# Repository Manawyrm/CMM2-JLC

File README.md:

Colour Maximite 2 - JLC-ready design
=============================

#### Overview

This is a open-source hardware clone PCB of the [Colour Maximite 2](https://geoffg.net/maximite.html) computer.  
It's fully compatible to the original firmware and software.  

- Designed for automated assembly at [JLCPCB](https://jlcpcb.com/DDE), everything except the connectors can be machine assembled.  
- USB-C port (instead of USB-B) for serial and power  
- microSD socket instead of full-size SD socket  
- STM32 and SDRAM directly onboard, no expensive evaluation board needed  

#### Bill of materials

[Interactive BOM](https://tbspace.de/content/downloads/ibom_cmm2_reve.html)

| Description | Part No.  | Links  |
| :-------:|-------------| -----:|
| 3.5mm audio jack | XKB PJ-3270 | [LCSC](https://lcsc.com/product-detail/Audio-Video-Connectors_XKB-Connectivity-PJ-3270_C381134.html) |
| microSD socket | HOAUC HYC77-TF09-200 | [LCSC](https://lcsc.com/product-detail/Card-Sockets-Connectors_HOAUC-HYC77-TF09-200_C341092.html)  |
| USB-C connector | Jing C167321 | [LCSC](https://lcsc.com/product-detail/USB-Connectors_Jing-Extension-of-the-Electronic-Co-C167321_C167321.html)  |
| USB-A connector | Jing C42650 | [LCSC](https://lcsc.com/product-detail/USB-Connectors_Jing-Extension-of-the-Electronic-Co-C42650_C42650.html)  |
| 40pin IDC | BOOMELE C9138 | [LCSC](https://lcsc.com/product-detail/IDC-Connectors_BOOMELE-Boom-Precision-Elec-C9138_C9138.html)  |
| VGA connector | CONNFLY DS1038-15FBNSiA74-0CC | [LCSC](https://lcsc.com/product-detail/D-Sub-Connectors_CONNFLY-Elec-DS1038-15FBNSiA74-0CC_C75754.html)  |

#### Footprint credits
| Author | Components  |
| ----- |-------|
| [Tobias Schramm](https://github.com/TobleMiner) | CR2032 Holder, 3.5mm Audiojack, MicroSD socket, reset button |
| [Jan Henrik Hemsing](https://github.com/Jan--Henrik) | Nunchuck connector |

#### Rev.A Errata
- Missing mounting holes
- SDRAM pinout is missing A12 line 
(causes instability, fixed in Rev.B, workaround with enamelled copper wire of the same length as the other traces)
- SRV05 diode package had the Pin 1 indicator at Pin 6.  
- Nunchuck footprint is reversed

#### Rev. B Errata
- KiCad Bug caused data corruption in PCB files, board files were reset back to pre-RevA state (missing via stitching). Will still work. 
- SRV05 diode package had the Pin 1 indicator at Pin 6.  
- Nunchuck footprint is reversed

#### Rev. C Errata
- SRV05 diode package had the Pin 1 indicator at Pin 6.  
- Nunchuck footprint is reversed

#### Rev. D Errata
- SRV05 diode package had the Pin 1 indicator at Pin 6.

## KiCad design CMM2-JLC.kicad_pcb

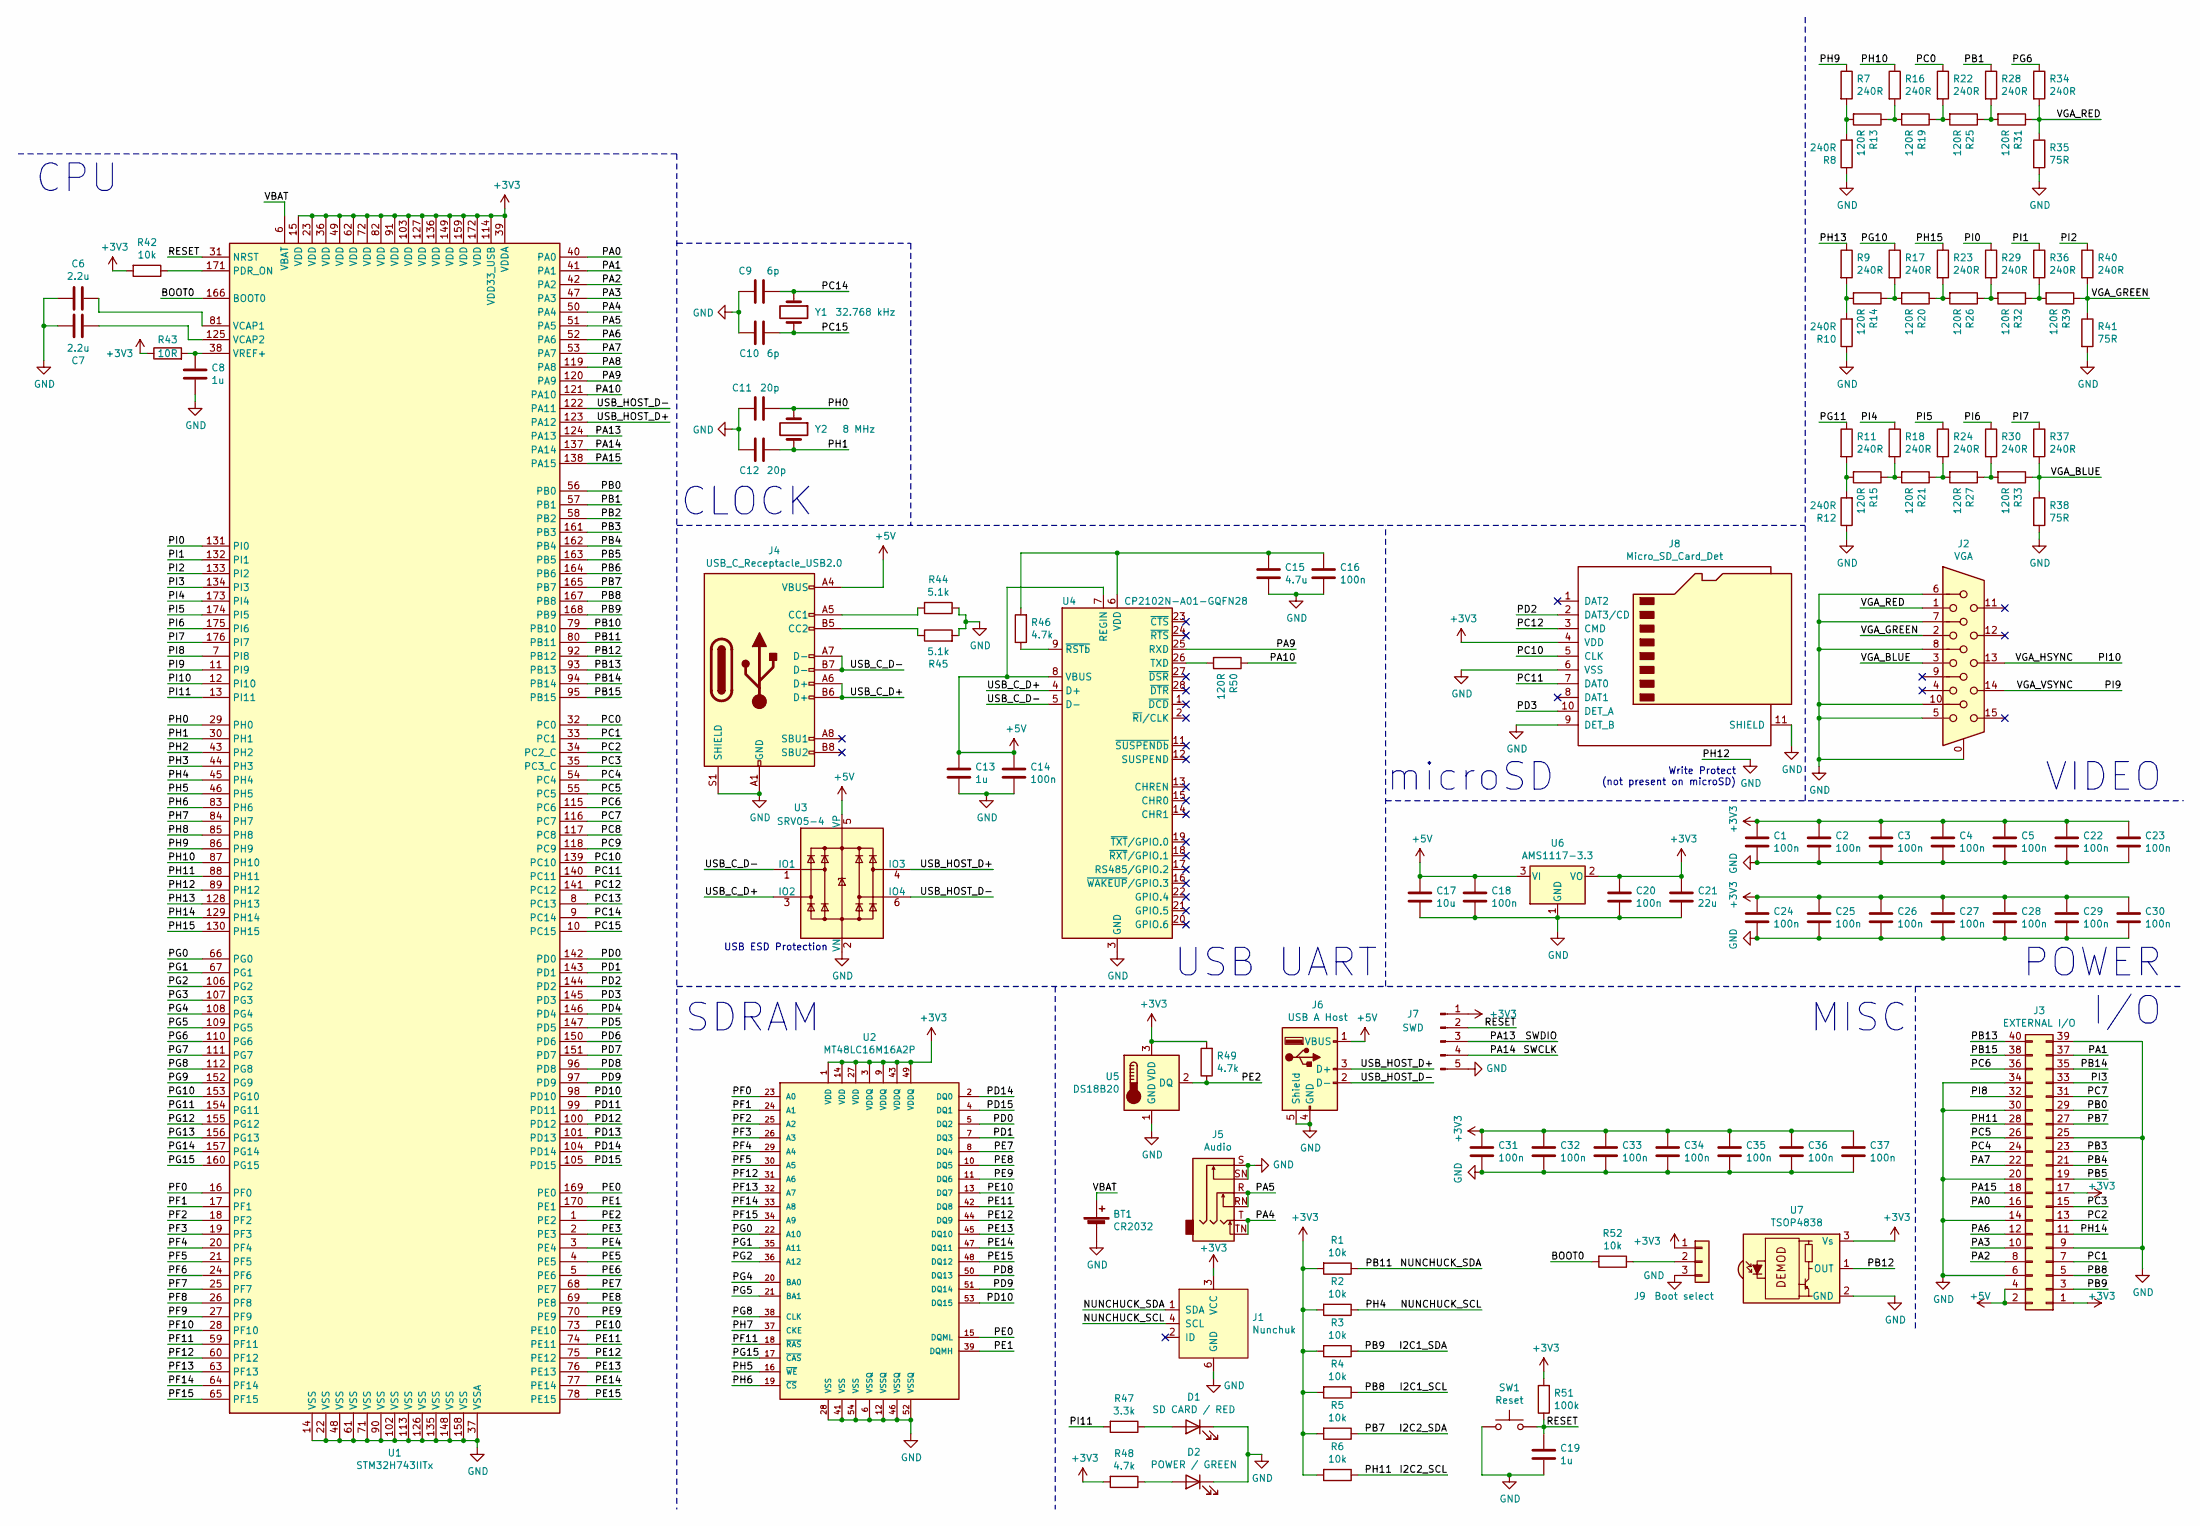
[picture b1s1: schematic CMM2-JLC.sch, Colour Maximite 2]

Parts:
BT1: CR2032; BatteryHolder_CR2032-BS-6-1; LCSC C70377
C1, C2, C3, C4, C5, C14, C16, C18, C20, C22, C23, C24, C25, C26, C27, C28, C29, C30, C31, C32, C33, C34, C35, C36, C37: 100n; C_0402_1005Metric; LCSC C1525
C6, C7: 2.2u; C_0603_1608Metric; LCSC C23630
C8, C13, C19: 1u; C_0402_1005Metric; LCSC C52923
C9, C10: 6p; C_0402_1005Metric; LCSC C30274
C11, C12: 20p; C_0402_1005Metric; LCSC C1554
C15: 4.7u; C_0402_1005Metric; LCSC C23733
C17: 10u; C_0603_1608Metric; LCSC C19702
C21: 22u; C_0603_1608Metric; LCSC C59461
D1: SD CARD / RED; LED_0603_1608Metric; LCSC C2286
D2: POWER / GREEN; LED_0603_1608Metric; LCSC C72043
J1: Nunchuk; nunchuck
J2: VGA; DSUB-15-HD_Female_Horizontal_P2.29x2,54mm_EdgePinOffset8.63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
J3: EXTERNAL I/O; IDC-Header_2x20_P2.54mm_Vertical
J4: USB_C_Receptacle_USB2.0; USB_C_Receptacle_Palconn_UTC16-G
J5: Audio; PJ-3270
J6: USB A Host; USB_A_Molex_67643_Horizontal
J7: SWD; PinHeader_1x05_P2.54mm_Vertical
J8: Micro_SD_Card_Det; HOAUC_HYC77-TF09-200
J9: Boot select; PinHeader_1x03_P2.54mm_Vertical
R1, R2, R3, R4, R5, R6, R42, R52: 10k; R_0402_1005Metric; LCSC C25744
R7, R8, R9, R10, R11, R12, R16, R17, R18, R22, R23, R24, R28, R29, R30, R34, R36, R37, R40: 240R; R_0603_1608Metric; LCSC C23350
R13, R14, R15, R19, R20, R21, R25, R26, R27, R31, R32, R33, R39, R50: 120R; R_0603_1608Metric; LCSC C22787
R35, R38, R41: 75R; R_0603_1608Metric; LCSC C4275
R43: 10R; R_0402_1005Metric; LCSC C25077
R44, R45: 5.1k; R_0402_1005Metric; LCSC C25905
R46, R48, R49: 4.7k; R_0402_1005Metric; LCSC C25900
R47: 3.3k; R_0402_1005Metric; LCSC C25890
R51: 100k; R_0402_1005Metric; LCSC C25741
SW1: Reset; TS-1187A-X-X-X; LCSC C318887
U1: STM32H743IITx; LQFP-176_24x24mm_P0.5mm; LCSC C89597
U2: MT48LC16M16A2P; TSOP-II-54_22.2x10.16mm_P0.8mm; LCSC C26393
U3: SRV05-4; SOT-23-6; LCSC C85364
U4: CP2102N-A01-GQFN28; QFN-28-1EP_5x5mm_P0.5mm_EP3.35x3.35mm; LCSC C6568
U5: DS18B20; TO-92_Inline
U6: AMS1117-3.3; SOT-223-3_TabPin2; LCSC C6186
U7: TSOP4838; Vishay_MOLD-3Pin
Y1: 32.768 kHz; Crystal_SMD_3215-2Pin_3.2x1.5mm; LCSC C32346
Y2: 8 MHz; Crystal_SMD_5032-2Pin_5.0x3.2mm; LCSC C115962

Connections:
+3V3: C1.1, C2.1, C3.1, C4.1, C5.1, C20.1, C21.1, C22.1, C23.1, C24.1, C25.1, C26.1, C27.1, C28.1, C29.1, C30.1, C31.1, C32.1, C33.1, C34.1, C35.1, C36.1, C37.1, J1.3 (VCC), J3.1, J3.17, J7.1, J8.4 (VDD), J9.1, R1.2, R2.2, R3.2, R4.2, R5.2, R6.2, R42.2, R43.1, R48.2, R49.2, R51.2, U1.15 (VDD), U1.23 (VDD), U1.36 (VDD), U1.39 (VDDA), U1.49 (VDD), U1.62 (VDD), U1.72 (VDD), U1.82 (VDD), U1.91 (VDD), U1.103 (VDD), U1.114 (VDD33_USB), U1.127 (VDD), U1.136 (VDD), U1.149 (VDD), U1.159 (VDD), U1.172 (VDD), U2.1 (VDD), U2.3 (VDDQ), U2.9 (VDDQ), U2.14 (VDD), U2.27 (VDD), U2.43 (VDDQ), U2.49 (VDDQ), U5.3 (VDD), U6.2 (VO), U7.3 (Vs)
+5V: C13.1, C14.1, C17.1, C18.1, J3.2, J3.4, J4.A4 (VBUS), J4.A9 (VBUS), J4.B4 (VBUS), J4.B9 (VBUS), J6.1 (VBUS), U3.5 (VP), U4.7 (REGIN), U4.8 (VBUS), U6.3 (VI)
/BOOT0: R52.2, U1.166 (BOOT0)
/I2C1_SCL: J3.5, R4.1, U1.167 (PB8)
/I2C1_SDA: J3.3, R3.1, U1.168 (PB9)
/I2C2_SCL: J3.28, R6.1, U1.88 (PH11)
/I2C2_SDA: J3.27, R5.1, U1.165 (PB7)
/NUNCHUCK_SCL: J1.4 (SCL), R2.1, U1.45 (PH4)
/NUNCHUCK_SDA: J1.1 (SDA), R1.1, U1.80 (PB11)
/PA0: J3.16, U1.40 (PA0)
/PA1: J3.37, U1.41 (PA1)
/PA2: J3.8, U1.42 (PA2)
/PA3: J3.10, U1.47 (PA3)
/PA4: J5.T, J5.TN, U1.50 (PA4)
/PA5: J5.R, J5.RN, U1.51 (PA5)
/PA6: J3.12, U1.52 (PA6)
/PA7: J3.22, U1.53 (PA7)
/PA8: U1.119 (PA8)
/PA9: U1.120 (PA9), U4.25 (RXD)
/PA10: R50.1, U1.121 (PA10)
/PA13: J7.3, U1.124 (PA13)
/PA14: J7.4, U1.137 (PA14)
/PA15: J3.18, U1.138 (PA15)
/PB0: J3.29, U1.56 (PB0)
/PB1: R28.1, U1.57 (PB1)
/PB2: U1.58 (PB2)
/PB3: J3.23, U1.161 (PB3)
/PB4: J3.21, U1.162 (PB4)
/PB5: J3.19, U1.163 (PB5)
/PB6: U1.164 (PB6)
/PB10: U1.79 (PB10)
/PB12: U1.92 (PB12), U7.1 (OUT)
/PB13: J3.40, U1.93 (PB13)
/PB14: J3.35, U1.94 (PB14)
/PB15: J3.38, U1.95 (PB15)
/PC0: R22.1, U1.32 (PC0)
/PC1: J3.7, U1.33 (PC1)
/PC2: J3.13, U1.34 (PC2_C)
/PC3: J3.15, U1.35 (PC3_C)
/PC4: J3.24, U1.54 (PC4)
/PC5: J3.26, U1.55 (PC5)
/PC6: J3.36, U1.115 (PC6)
/PC7: J3.31, U1.116 (PC7)
/PC8: U1.117 (PC8)
/PC9: U1.118 (PC9)
/PC10: J8.5 (CLK), U1.139 (PC10)
/PC11: J8.7 (DAT0), U1.140 (PC11)
/PC12: J8.3 (CMD), U1.141 (PC12)
/PC13: U1.8 (PC13)
/PC14: C9.2, U1.9 (PC14), Y1.1
/PC15: C10.1, U1.10 (PC15), Y1.2
/PD0: U1.142 (PD0), U2.5 (DQ2)
/PD1: U1.143 (PD1), U2.7 (DQ3)
/PD2: J8.2 (DAT3/CD), U1.144 (PD2)
/PD3: J8.10 (DET_A), U1.145 (PD3)
/PD4: U1.146 (PD4)
/PD5: U1.147 (PD5)
/PD6: U1.150 (PD6)
/PD7: U1.151 (PD7)
/PD8: U1.96 (PD8), U2.50 (DQ13)
/PD9: U1.97 (PD9), U2.51 (DQ14)
/PD10: U1.98 (PD10), U2.53 (DQ15)
/PD11: U1.99 (PD11)
/PD12: U1.100 (PD12)
/PD13: U1.101 (PD13)
/PD14: U1.104 (PD14), U2.2 (DQ0)
/PD15: U1.105 (PD15), U2.4 (DQ1)
/PE0: U1.169 (PE0), U2.15 (DQML)
/PE1: U1.170 (PE1), U2.39 (DQMH)
/PE2: R49.1, U1.1 (PE2), U5.2 (DQ)
/PE3: U1.2 (PE3)
/PE4: U1.3 (PE4)
/PE5: U1.4 (PE5)
/PE6: U1.5 (PE6)
/PE7: U1.68 (PE7), U2.8 (DQ4)
/PE8: U1.69 (PE8), U2.10 (DQ5)
/PE9: U1.70 (PE9), U2.11 (DQ6)
/PE10: U1.73 (PE10), U2.13 (DQ7)
/PE11: U1.74 (PE11), U2.42 (DQ8)
/PE12: U1.75 (PE12), U2.44 (DQ9)
/PE13: U1.76 (PE13), U2.45 (DQ10)
/PE14: U1.77 (PE14), U2.47 (DQ11)
/PE15: U1.78 (PE15), U2.48 (DQ12)
/PF0: U1.16 (PF0), U2.23 (A0)
/PF1: U1.17 (PF1), U2.24 (A1)
/PF2: U1.18 (PF2), U2.25 (A2)
/PF3: U1.19 (PF3), U2.26 (A3)
/PF4: U1.20 (PF4), U2.29 (A4)
/PF5: U1.21 (PF5), U2.30 (A5)
/PF6: U1.24 (PF6)
/PF7: U1.25 (PF7)
/PF8: U1.26 (PF8)
/PF9: U1.27 (PF9)
/PF10: U1.28 (PF10)
/PF11: U1.59 (PF11), U2.18 (~RAS~)
/PF12: U1.60 (PF12), U2.31 (A6)
/PF13: U1.63 (PF13), U2.32 (A7)
/PF14: U1.64 (PF14), U2.33 (A8)
/PF15: U1.65 (PF15), U2.34 (A9)
/PG0: U1.66 (PG0), U2.22 (A10)
/PG1: U1.67 (PG1), U2.35 (A11)
/PG2: U1.106 (PG2), U2.36 (A12)
/PG3: U1.107 (PG3)
/PG4: U1.108 (PG4), U2.20 (BA0)
/PG5: U1.109 (PG5), U2.21 (BA1)
/PG6: R34.1, U1.110 (PG6)
/PG7: U1.111 (PG7)
/PG8: U1.112 (PG8), U2.38 (CLK)
/PG9: U1.152 (PG9)
/PG10: R17.1, U1.153 (PG10)
/PG11: R11.1, U1.154 (PG11)
/PG12: U1.155 (PG12)
/PG13: U1.156 (PG13)
/PG14: U1.157 (PG14)
/PG15: U1.160 (PG15), U2.17 (~CAS~)
/PH0: C11.2, U1.29 (PH0), Y2.1
/PH1: C12.1, U1.30 (PH1), Y2.2
/PH2: U1.43 (PH2)
/PH3: U1.44 (PH3)
/PH5: U1.46 (PH5), U2.16 (~WE~)
/PH6: U1.83 (PH6), U2.19 (~CS~)
/PH7: U1.84 (PH7), U2.37 (CKE)
/PH8: U1.85 (PH8)
/PH9: R7.1, U1.86 (PH9)
/PH10: R16.1, U1.87 (PH10)
/PH13: R9.1, U1.128 (PH13)
/PH14: J3.11, U1.129 (PH14)
/PH15: R23.1, U1.130 (PH15)
/PI0: R29.1, U1.131 (PI0)
/PI1: R36.1, U1.132 (PI1)
/PI2: R40.1, U1.133 (PI2)
/PI3: J3.33, U1.134 (PI3)
/PI4: R18.1, U1.173 (PI4)
/PI5: R24.1, U1.174 (PI5)
/PI6: R30.1, U1.175 (PI6)
/PI7: R37.1, U1.176 (PI7)
/PI8: J3.32, U1.7 (PI8)
/PI9: J2.14, U1.11 (PI9)
/PI10: J2.13, U1.12 (PI10)
/PI11: R47.2, U1.13 (PI11)
/RESET: C19.1, J7.2, R51.1, SW1.2, U1.31 (NRST)
/USB_C_D+: J4.A6 (D+), J4.B6 (D+), U3.3 (IO2), U4.4 (D+)
/USB_C_D-: J4.A7 (D-), J4.B7 (D-), U3.1 (IO1), U4.5 (D-)
/USB_HOST_D+: J6.3 (D+), U1.123 (PA12), U3.4 (IO3)
/USB_HOST_D-: J6.2 (D-), U1.122 (PA11), U3.6 (IO4)
/VBAT: BT1.1 (+), U1.6 (VBAT)
/VGA_BLUE: J2.3, R33.1, R37.2, R38.1
/VGA_GREEN: J2.2, R39.1, R40.2, R41.1
/VGA_RED: J2.1, R31.1, R34.2, R35.1
GND: BT1.2 (-), C1.2, C2.2, C3.2, C4.2, C5.2, C6.2, C7.1, C8.2, C9.1, C10.2, C11.1, C12.2, C13.2, C14.2, C15.2, C16.2, C17.2, C18.2, C19.2, C20.2, C21.2, C22.2, C23.2, C24.2, C25.2, C26.2, C27.2, C28.2, C29.2, C30.2, C31.2, C32.2, C33.2, C34.2, C35.2, C36.2, C37.2, D1.1 (K), D2.1 (K), J1.6 (GND), J2.0, J2.5, J2.6, J2.7, J2.8, J2.10, J3.6, J3.9, J3.14, J3.20, J3.25, J3.30, J3.34, J3.39, J4.A1 (GND), J4.A12 (GND), J4.B1 (GND), J4.B12 (GND), J4.S1 (SHIELD), J5.S, J5.SN, J6.4 (GND), J6.5 (Shield), J7.5, J8.6 (VSS), J8.9 (DET_B), J8.11 (SHIELD), J9.3, R8.1, R10.1, R12.1, R35.2, R38.2, R41.2, R44.1, R45.2, SW1.1, U1.14 (VSS), U1.22 (VSS), U1.37 (VSSA), U1.48 (VSS), U1.61 (VSS), U1.71 (VSS), U1.89 (PH12), U1.90 (VSS), U1.102 (VSS), U1.113 (VSS), U1.126 (VSS), U1.135 (VSS), U1.148 (VSS), U1.158 (VSS), U2.6 (VSSQ), U2.12 (VSSQ), U2.28 (VSS), U2.41 (VSS), U2.46 (VSSQ), U2.52 (VSSQ), U2.54 (VSS), U3.2 (VN), U4.3 (GND), U4.29 (GND), U5.1 (GND), U6.1 (GND), U7.2 (GND)
unnamed: C6.1, U1.81 (VCAP1)
unnamed: C7.2, U1.125 (VCAP2)
unnamed: C8.1, R43.2, U1.38 (VREF+)
unnamed: C15.1, C16.1, R46.2, U4.6 (VDD)
unnamed: D1.2 (A), R47.1
unnamed: D2.2 (A), R48.1
unnamed: J4.A5 (CC1), R44.2
unnamed: J4.B5 (CC2), R45.1
unnamed: J9.2, R52.1
unnamed: R9.2, R10.2, R14.2
unnamed: R11.2, R12.2, R15.2
unnamed: R13.1, R16.2, R19.2
unnamed: R7.2, R8.2, R13.2
unnamed: R14.1, R17.2, R20.2
unnamed: R15.1, R18.2, R21.2
unnamed: R19.1, R22.2, R25.2
unnamed: R20.1, R23.2, R26.2
unnamed: R21.1, R24.2, R27.2
unnamed: R25.1, R28.2, R31.2
unnamed: R26.1, R29.2, R32.2
unnamed: R27.1, R30.2, R33.2
unnamed: R32.1, R36.2, R39.2
unnamed: R42.1, U1.171 (PDR_ON)
unnamed: R46.1, U4.9 (~RSTb)
unnamed: R50.2, U4.26 (TXD)

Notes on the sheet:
SDRAM
CPU
VIDEO
I/O
MISC
USB ESD Protection
USB UART
POWER
Write Protect (not present on microSD)
microSD
CLOCK

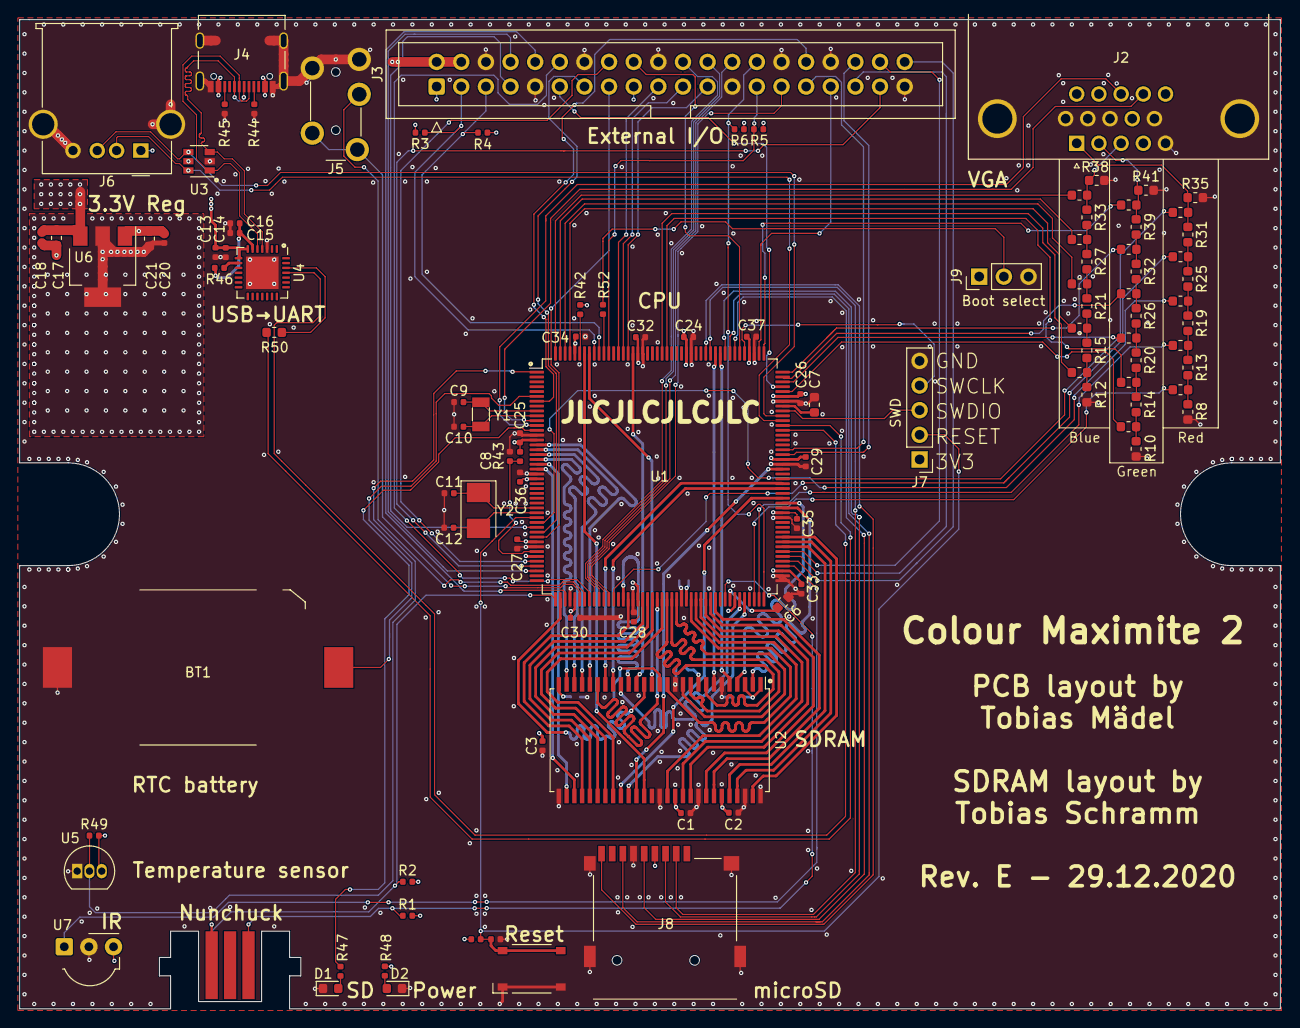
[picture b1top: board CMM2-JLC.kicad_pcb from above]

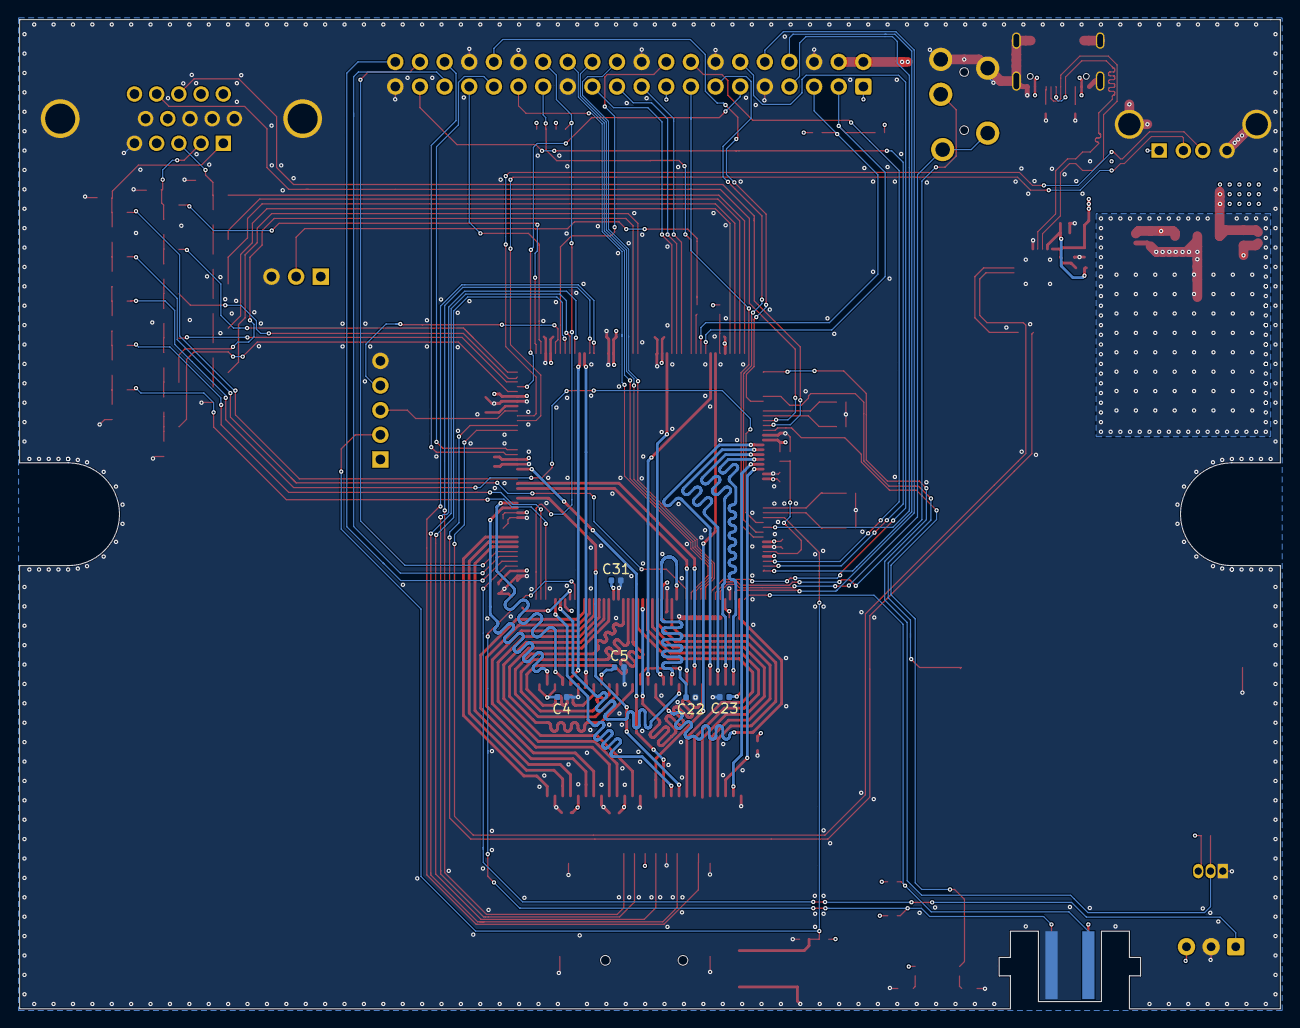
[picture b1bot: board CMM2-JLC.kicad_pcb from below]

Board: 4 copper layers, 130.0 x 102.0 mm, 111 parts (5 on the bottom side), 143 nets.

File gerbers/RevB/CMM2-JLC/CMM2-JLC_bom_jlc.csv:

"Comment","Designator","Footprint","LCSC Part #"
"CR2032","BT1","BatteryHolder_CR2032-BS-6-1","C70377"
"100n","C1,C2,C3,C4,C5,C14,C16,C20,C18,C22,C23,C24,C25,C26,C27,C28,C29,C30,C31,C32,C33,C34,C35,C36,C37","C_0402_1005Metric","C1525"
"2.2u","C6,C7","C_0603_1608Metric","C23630"
"6p","C9,C10","C_0402_1005Metric","C30274"
"20p","C11,C12","C_0402_1005Metric","C1554"
"1u","C13,C8,C19","C_0402_1005Metric","C52923"
"4.7u","C15","C_0402_1005Metric","C23733"
"10u","C17","C_0603_1608Metric","C19702"
"22u","C21","C_0603_1608Metric","C59461"
"SD CARD / RED","D1","LED_0603_1608Metric","C2286"
"POWER / GREEN","D2","LED_0603_1608Metric","C72043"
"10k","R1,R2,R3,R4,R5,R6,R42,R52","R_0402_1005Metric","C25744"
"240R","R7,R16,R22,R28,R8,R34,R11,R18,R24,R30,R12,R37,R9,R17,R23,R29,R10,R40,R36","R_0603_1608Metric","C23350"
"120R","R13,R19,R25,R31,R15,R21,R27,R33,R14,R20,R26,R39,R32,R50","R_0603_1608Metric","C22787"
"75R","R35,R38,R41","R_0603_1608Metric","C4275"
"10R","R43","R_0402_1005Metric","C25077"
"5.1k","R44,R45","R_0402_1005Metric","C25905"
"3.3k","R47","R_0402_1005Metric","C25890"
"4.7k","R48,R49,R46","R_0402_1005Metric","C25900"
"100k","R51","R_0402_1005Metric","C25741"
"Reset","SW1","TS-1187A-X-X-X","C318887"
"STM32H743IITx","U1","LQFP-176_24x24mm_P0.5mm","C89597"
"MT48LC16M16A2P","U2","TSOP-II-54_22.2x10.16mm_P0.8mm","C26393"
"SRV05-4","U3","SOT-23-6","C85364"
"CP2102N-A01-GQFN28","U4","QFN-28-1EP_5x5mm_P0.5mm_EP3.35x3.35mm","C6568"
"AMS1117-3.3","U6","SOT-223-3_TabPin2","C6186"
"32.768 kHz","Y1","Crystal_SMD_3215-2Pin_3.2x1.5mm","C32346"
"8 MHz","Y2","Crystal_SMD_5032-2Pin_5.0x3.2mm","C115962"

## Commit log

2020-07-05 Create LICENSE
2020-07-05 Add Readme
2020-07-05 Add USB-UART, power, microSD
2020-07-05 Add bootstrap circuitry
2020-07-05 Add footprints and crystals
2020-07-05 Add board outline
2020-07-05 remove unneccessary images
2020-07-05 first sdram routing
2020-07-05 sdram routed
2020-07-05 first component routing
2020-07-11 before SDRAM re-route
2020-07-11 Ignore log files
2020-07-11 Layout SDRAM
2020-07-11 VGA DAC gelayoutet
2020-07-11 VGA Routing
2020-07-11 Replace VGA connector
2020-07-11 USB Host routed
2020-07-12 Add decoupling, start routing of 40pin extension header
2020-07-14 Add microSD routing
2020-07-14 add 40pin expansion header routing
2020-07-14 Routed USB, UART and reset pins
2020-07-15 Add CP2102 routing
2020-07-15 Cleanup silkscreen, add credits
2020-07-15 Add pin1 markers and revA gerbers
2020-07-15 Fix reversed SDRAM bank select and some style/DRC issues
2020-07-15 Add final revA gerber
2020-07-15 Add final-2 revA gerber
2020-07-31 Rev B: Hook up SDRAM address line A12
    The old sdram symbol did not fit the sdram used. This commit introduces a
    new sdram symbol with address line A12 and bumps the revision to Rev B.
2020-08-08 Update board
    Last save seems incomplete?!
2020-08-08 Add proper readme and ibom
2020-08-11 Rev C
    Some (mostly cosmetic) changes from the final Rev A gerbers were lost in
    Rev B due to a corrupted .kicad_pcb file.
    This revision reintroduces those changes and improves overall attachment
    of groundplanes and islands to one another. Additionally the VGA connector
    footprint has been updated to fit the LCSC connector better.
    Changelog:
2020-08-24 Rev D
    Changelog:
    * Fix 180° rotated Nunchuk connector
2020-12-29 Fix pin one marker on USB protection diode
    Previously the marker indicated 180 degree rotation of the part.
2020-12-29 RevE
